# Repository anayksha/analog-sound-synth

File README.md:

# Analog sound synth

I think its analog idk

TODO: write readme

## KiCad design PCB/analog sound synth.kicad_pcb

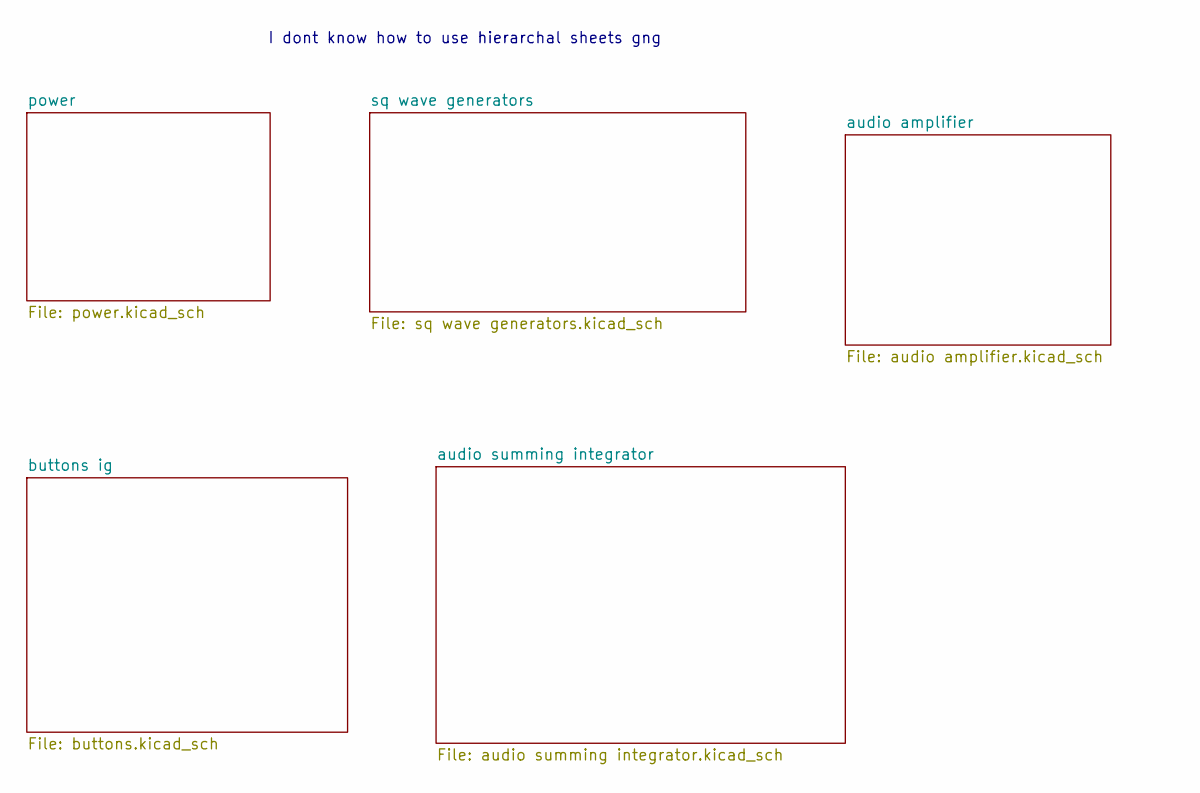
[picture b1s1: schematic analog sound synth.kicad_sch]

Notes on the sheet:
I dont know how to use hierarchal sheets gng

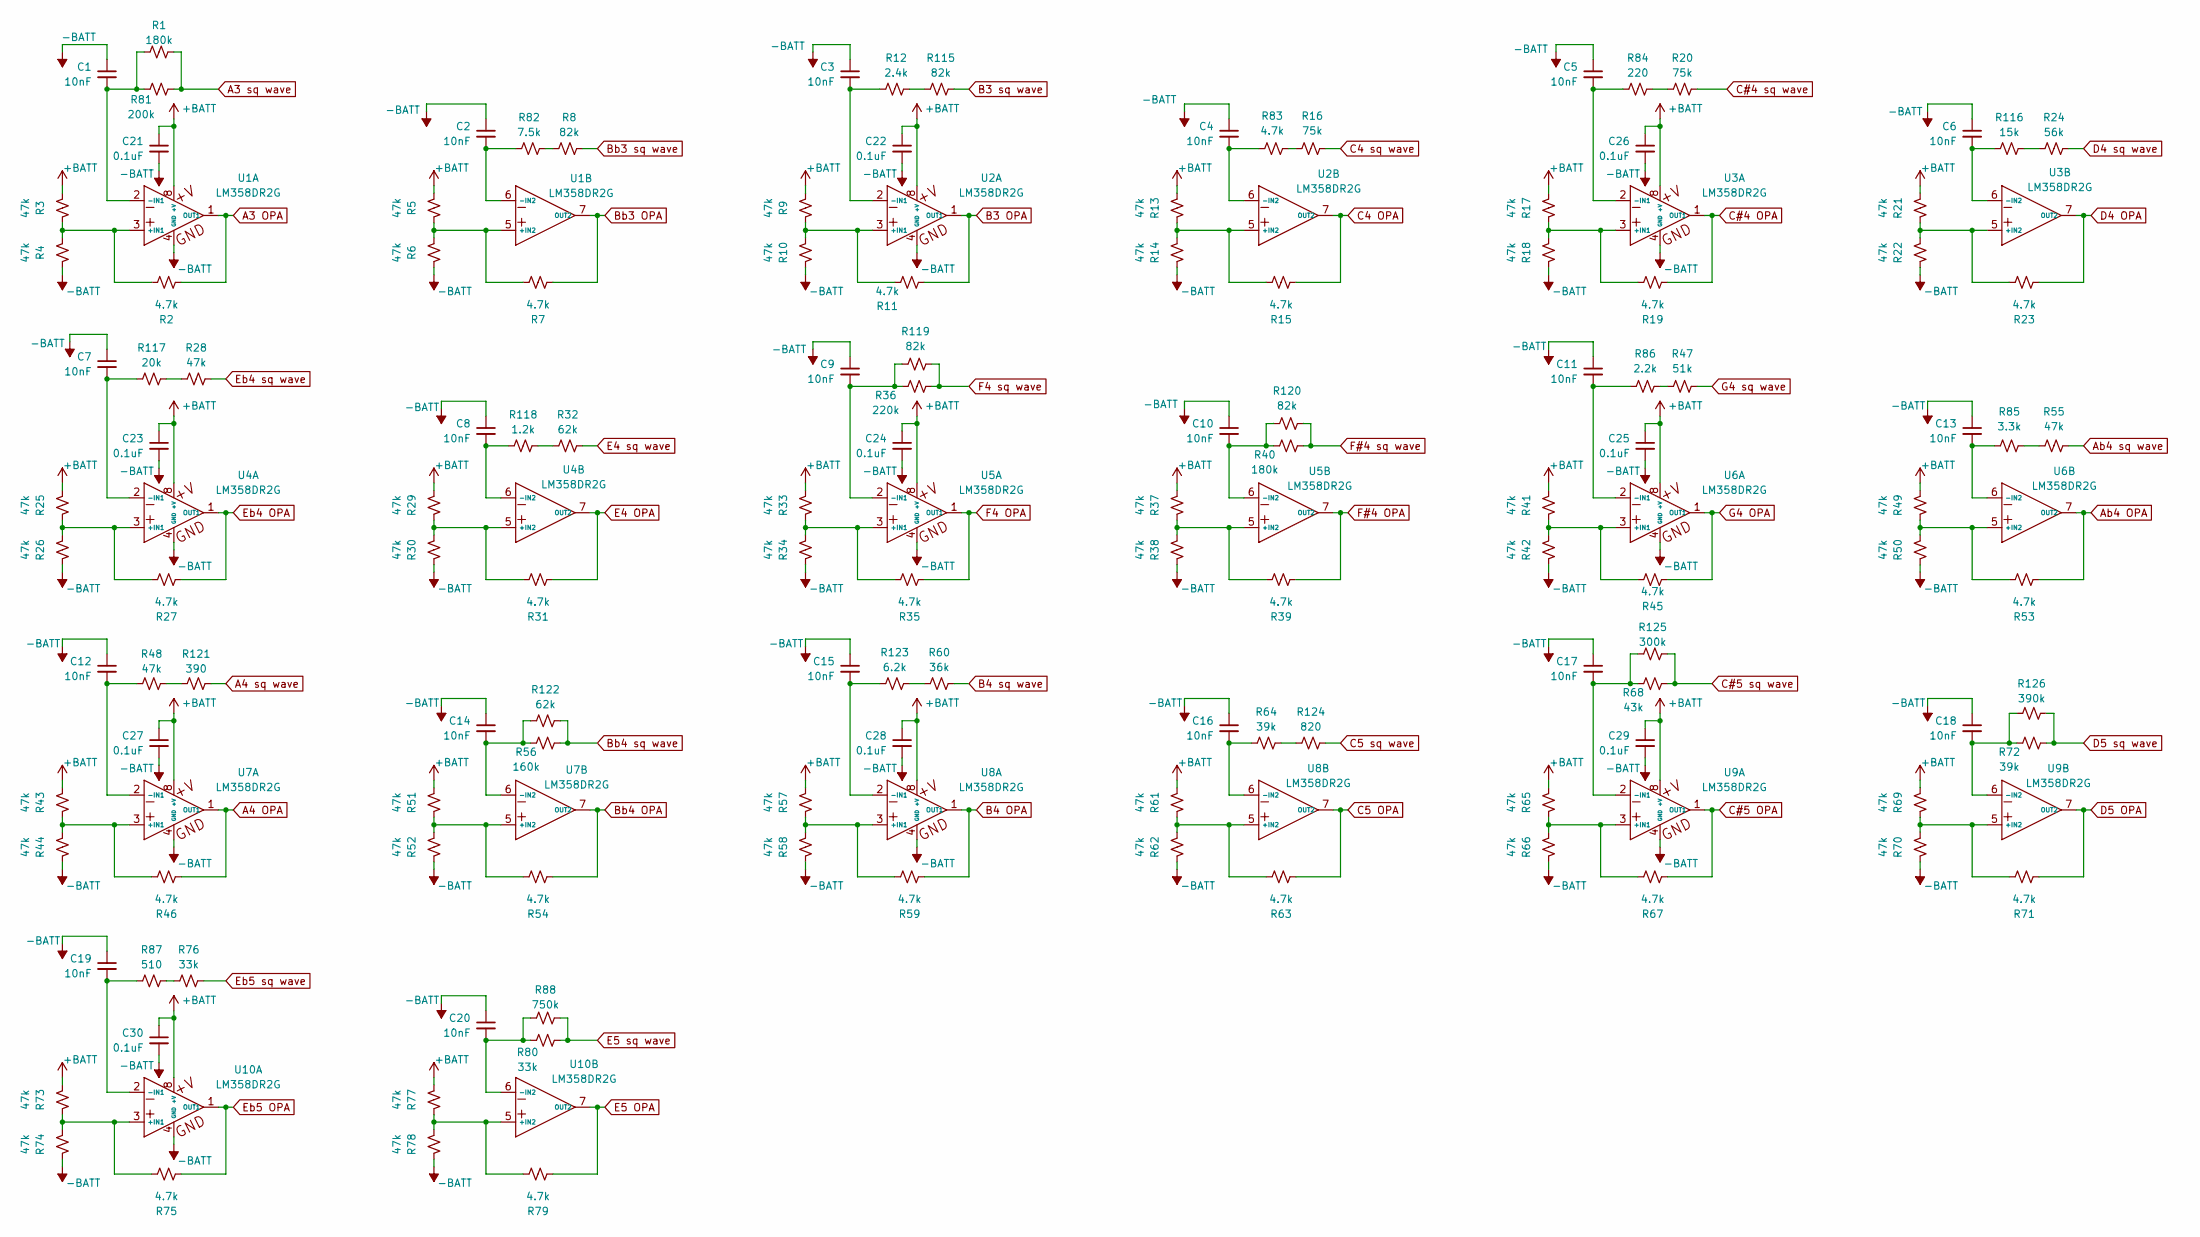
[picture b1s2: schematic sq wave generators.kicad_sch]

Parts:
C1, C2, C3, C4, C5, C6, C7, C8, C9, C10, C11, C12, C13, C14, C15, C16, C17, C18, C19, C20: 10nF; C_0603_1608Metric
C21, C22, C23, C24, C25, C26, C27, C28, C29, C30: 0.1uF; C_0402_1005Metric
R1, R40: 180k; R_0603_1608Metric
R2, R7, R11, R15, R19, R23, R27, R31, R35, R39, R45, R46, R53, R54, R59, R63, R67, R71, R75, R79, R83: 4.7k; R_0402_1005Metric
R3, R4, R5, R6, R9, R10, R13, R14, R17, R18, R21, R22, R25, R26, R28, R29, R30, R33, R34, R37, R38, R41, R42, R43, R44, R48, R49, R50, R51, R52, R55, R57, R58, R61, R62, R65, R66, R69, R70, R73, R74, R77, R78: 47k; R_0402_1005Metric
R8, R115, R119, R120: 82k; R_0603_1608Metric
R12: 2.4k; R_0402_1005Metric
R16, R20: 75k; R_0402_1005Metric
R24: 56k; R_0402_1005Metric
R32, R122: 62k; R_0603_1608Metric
R36: 220k; R_0402_1005Metric
R47: 51k; R_0402_1005Metric
R56: 160k; R_0603_1608Metric
R60: 36k; R_0603_1608Metric
R64, R72: 39k; R_0402_1005Metric
R68: 43k; R_0603_1608Metric
R76, R80: 33k; R_0402_1005Metric
R81: 200k; R_0402_1005Metric
R82: 7.5k; R_0402_1005Metric
R84: 220; R_0402_1005Metric
R85: 3.3k; R_0402_1005Metric
R86: 2.2k; R_0402_1005Metric
R87: 510; R_0402_1005Metric
R88: 750k; R_0603_1608Metric
R116: 15k; R_0402_1005Metric
R117: 20k; R_0402_1005Metric
R118: 1.2k; R_0402_1005Metric
R121: 390; R_0603_1608Metric
R123: 6.2k; R_0603_1608Metric
R124: 820; R_0603_1608Metric
R125: 300k; R_0402_1005Metric
R126: 390k; R_0603_1608Metric
U1, U2, U3, U4, U5, U6, U7, U8, U9, U10: LM358DR2G; SOIC-8_L5.0-W4.0-P1.27-LS6.0-BL; MPN LM358DR2G; LCSC Part C7950

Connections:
+BATT: C21.1, C22.1, C23.1, C24.1, C25.1, C26.1, C27.1, C28.1, C29.1, C30.1, R3.2, R5.2, R9.2, R13.2, R17.2, R21.2, R25.2, R29.2, R33.2, R37.2, R41.2, R43.2, R49.2, R51.2, R57.2, R61.2, R65.2, R69.2, R73.2, R77.2, U1.8 (+V), U2.8 (+V), U3.8 (+V), U4.8 (+V), U5.8 (+V), U6.8 (+V), U7.8 (+V), U8.8 (+V), U9.8 (+V), U10.8 (+V); also elsewhere on the board
-BATT: C1.1, C2.1, C3.1, C4.1, C5.1, C6.1, C7.1, C8.1, C9.1, C10.1, C11.1, C12.1, C13.1, C14.1, C15.1, C16.1, C17.1, C18.1, C19.1, C20.1, C21.2, C22.2, C23.2, C24.2, C25.2, C26.2, C27.2, C28.2, C29.2, C30.2, R4.1, R6.1, R10.1, R14.1, R18.1, R22.1, R26.1, R30.1, R34.1, R38.1, R42.1, R44.1, R50.1, R52.1, R58.1, R62.1, R66.1, R70.1, R74.1, R78.1, U1.4 (GND), U2.4 (GND), U3.4 (GND), U4.4 (GND), U5.4 (GND), U6.4 (GND), U7.4 (GND), U8.4 (GND), U9.4 (GND), U10.4 (GND); also elsewhere on the board
A3 OPA: R2.2, U1.1 (OUT1); also elsewhere on the board
A3 sq wave: R1.2, R81.2; also elsewhere on the board
A4 OPA: R46.2, U7.1 (OUT1); also elsewhere on the board
A4 sq wave: R121.2; also elsewhere on the board
Ab4 OPA: R53.2, U6.7 (OUT2); also elsewhere on the board
Ab4 sq wave: R55.2; also elsewhere on the board
B3 OPA: R11.2, U2.1 (OUT1); also elsewhere on the board
B3 sq wave: R115.2; also elsewhere on the board
B4 OPA: R59.2, U8.1 (OUT1); also elsewhere on the board
B4 sq wave: R60.2; also elsewhere on the board
Bb3 OPA: R7.2, U1.7 (OUT2); also elsewhere on the board
Bb3 sq wave: R8.2; also elsewhere on the board
Bb4 OPA: R54.2, U7.7 (OUT2); also elsewhere on the board
Bb4 sq wave: R56.2, R122.2; also elsewhere on the board
C4 OPA: R15.2, U2.7 (OUT2); also elsewhere on the board
C4 sq wave: R16.2; also elsewhere on the board
C5 OPA: R63.2, U8.7 (OUT2); also elsewhere on the board
C5 sq wave: R124.2; also elsewhere on the board
C#4 OPA: R19.2, U3.1 (OUT1); also elsewhere on the board
C#4 sq wave: R20.2; also elsewhere on the board
C#5 OPA: R67.2, U9.1 (OUT1); also elsewhere on the board
C#5 sq wave: R68.2, R125.2; also elsewhere on the board
D4 OPA: R23.2, U3.7 (OUT2); also elsewhere on the board
D4 sq wave: R24.2; also elsewhere on the board
D5 OPA: R71.2, U9.7 (OUT2); also elsewhere on the board
D5 sq wave: R72.2, R126.2; also elsewhere on the board
E4 OPA: R31.2, U4.7 (OUT2); also elsewhere on the board
E4 sq wave: R32.2; also elsewhere on the board
E5 OPA: R79.2, U10.7 (OUT2); also elsewhere on the board
E5 sq wave: R80.2, R88.2; also elsewhere on the board
Eb4 OPA: R27.2, U4.1 (OUT1); also elsewhere on the board
Eb4 sq wave: R28.2; also elsewhere on the board
Eb5 OPA: R75.2, U10.1 (OUT1); also elsewhere on the board
Eb5 sq wave: R76.2; also elsewhere on the board
F4 OPA: R35.2, U5.1 (OUT1); also elsewhere on the board
F4 sq wave: R36.2, R119.2; also elsewhere on the board
F#4 OPA: R39.2, U5.7 (OUT2); also elsewhere on the board
F#4 sq wave: R40.2, R120.2; also elsewhere on the board
G4 OPA: R45.2, U6.1 (OUT1); also elsewhere on the board
G4 sq wave: R47.2; also elsewhere on the board
unnamed: R8.1, R82.2
unnamed: R16.1, R83.2
unnamed: R20.1, R84.2
unnamed: R47.1, R86.2
unnamed: R55.1, R85.2
unnamed: R76.1, R87.2
unnamed: R12.2, R115.1
unnamed: R24.1, R116.2
unnamed: R28.1, R117.2
unnamed: R32.1, R118.2
unnamed: R48.2, R121.1
unnamed: R60.1, R123.2
unnamed: R64.2, R124.1
unnamed: R2.1, R3.1, R4.2, U1.3 (+IN1)
unnamed: C1.2, R1.1, R81.1, U1.2 (-IN1)
unnamed: R5.1, R6.2, R7.1, U1.5 (+IN2)
unnamed: C2.2, R82.1, U1.6 (-IN2)
unnamed: R9.1, R10.2, R11.1, U2.3 (+IN1)
unnamed: C3.2, R12.1, U2.2 (-IN1)
unnamed: R13.1, R14.2, R15.1, U2.5 (+IN2)
unnamed: C4.2, R83.1, U2.6 (-IN2)
unnamed: R17.1, R18.2, R19.1, U3.3 (+IN1)
unnamed: C5.2, R84.1, U3.2 (-IN1)
unnamed: R21.1, R22.2, R23.1, U3.5 (+IN2)
unnamed: C6.2, R116.1, U3.6 (-IN2)
unnamed: R25.1, R26.2, R27.1, U4.3 (+IN1)
unnamed: C7.2, R117.1, U4.2 (-IN1)
unnamed: R29.1, R30.2, R31.1, U4.5 (+IN2)
unnamed: C8.2, R118.1, U4.6 (-IN2)
unnamed: R33.1, R34.2, R35.1, U5.3 (+IN1)
unnamed: C9.2, R36.1, R119.1, U5.2 (-IN1)
unnamed: R37.1, R38.2, R39.1, U5.5 (+IN2)
unnamed: C10.2, R40.1, R120.1, U5.6 (-IN2)
unnamed: R41.1, R42.2, R45.1, U6.3 (+IN1)
unnamed: C11.2, R86.1, U6.2 (-IN1)
unnamed: R49.1, R50.2, R53.1, U6.5 (+IN2)
unnamed: C13.2, R85.1, U6.6 (-IN2)
unnamed: R43.1, R44.2, R46.1, U7.3 (+IN1)
unnamed: C12.2, R48.1, U7.2 (-IN1)
unnamed: R51.1, R52.2, R54.1, U7.5 (+IN2)
unnamed: C14.2, R56.1, R122.1, U7.6 (-IN2)
unnamed: R57.1, R58.2, R59.1, U8.3 (+IN1)
unnamed: C15.2, R123.1, U8.2 (-IN1)
unnamed: R61.1, R62.2, R63.1, U8.5 (+IN2)
unnamed: C16.2, R64.1, U8.6 (-IN2)
unnamed: R65.1, R66.2, R67.1, U9.3 (+IN1)
unnamed: C17.2, R68.1, R125.1, U9.2 (-IN1)
unnamed: R69.1, R70.2, R71.1, U9.5 (+IN2)
unnamed: C18.2, R72.1, R126.1, U9.6 (-IN2)
unnamed: R73.1, R74.2, R75.1, U10.3 (+IN1)
unnamed: C19.2, R87.1, U10.2 (-IN1)
unnamed: R77.1, R78.2, R79.1, U10.5 (+IN2)
unnamed: C20.2, R80.1, R88.1, U10.6 (-IN2)

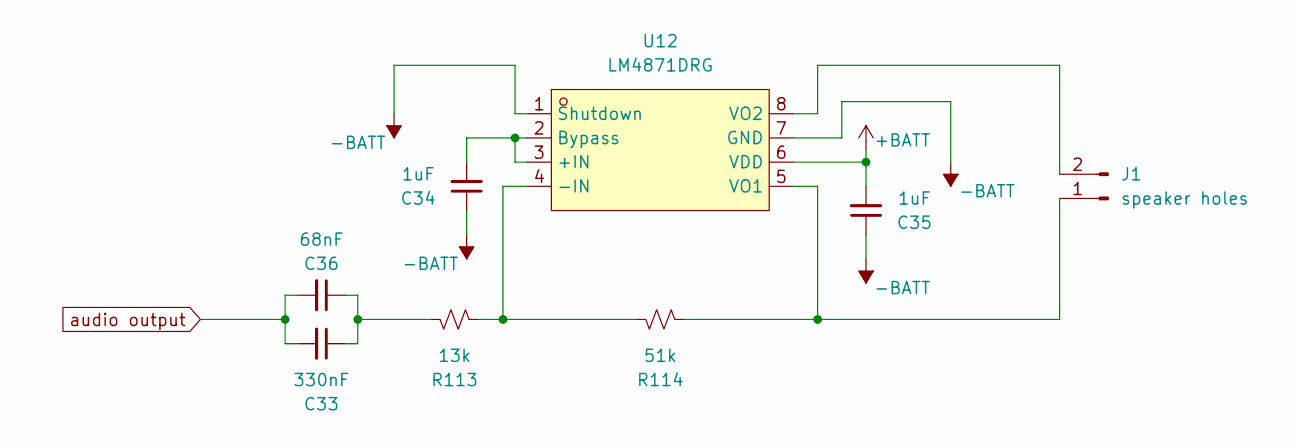
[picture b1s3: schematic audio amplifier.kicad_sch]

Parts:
C33: 330nF; C_0603_1608Metric
C34, C35: 1uF; C_0402_1005Metric
C36: 68nF; C_0603_1608Metric
J1: speaker holes; SolderWire-0.15sqmm_1x02_P4mm_D0.5mm_OD1.5mm_Relief
R113: 13k; R_0603_1608Metric
R114: 51k; R_0402_1005Metric
U12: LM4871DRG; SOP-8_L4.9-W3.9-P1.27-LS6.0-BL; MPN LM4871DRG; LCSC Part C2977084

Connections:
+BATT: C35.2, U12.6 (VDD); also elsewhere on the board
-BATT: C34.1, C35.1, U12.1 (Shutdown), U12.7 (GND); also elsewhere on the board
unnamed: C33.1, C36.1, R113.1
unnamed: J1.1, R114.2, U12.5 (VO1)
unnamed: J1.2, U12.8 (VO2)
unnamed: C34.2, U12.2 (Bypass), U12.3 (+IN)
unnamed: R113.2, R114.1, U12.4 (-IN)
audio output: C33.2, C36.2; also elsewhere on the board

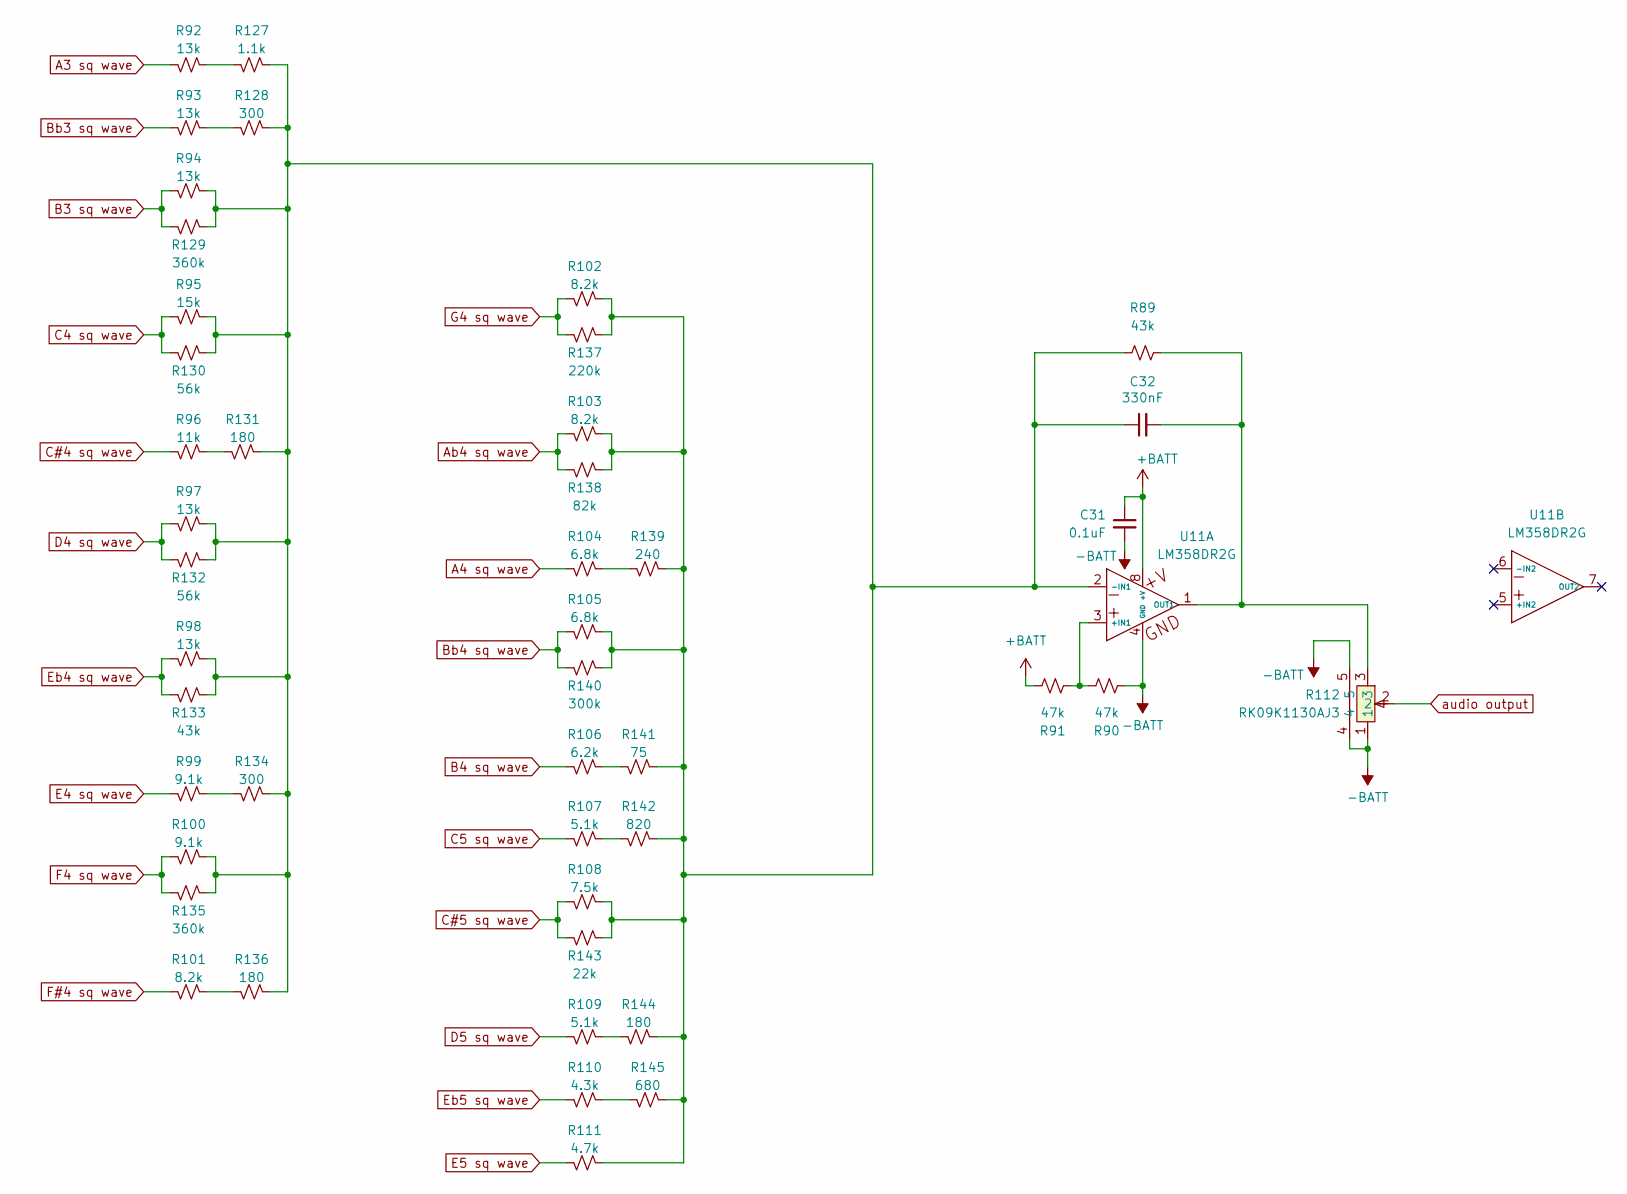
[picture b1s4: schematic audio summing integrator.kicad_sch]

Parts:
C31: 0.1uF; C_0402_1005Metric
C32: 330nF; C_0603_1608Metric
R89, R133: 43k; R_0603_1608Metric
R90, R91: 47k; R_0402_1005Metric
R92, R93, R94, R97, R98: 13k; R_0603_1608Metric
R95: 15k; R_0402_1005Metric
R96: 11k; R_0603_1608Metric
R99, R100: 9.1k; R_0603_1608Metric
R101, R102, R103: 8.2k; R_0402_1005Metric
R104, R105: 6.8k; R_0603_1608Metric
R106: 6.2k; R_0603_1608Metric
R107, R109: 5.1k; R_0402_1005Metric
R108: 7.5k; R_0402_1005Metric
R110: 4.3k; R_0603_1608Metric
R111: 4.7k; R_0402_1005Metric
R112: RK09K1130AJ3; RES-ADJ-TH_RK09K1130AJ3; MPN RK09K1130AJ3; LCSC Part C388854
R127: 1.1k; R_0603_1608Metric
R128, R134: 300; R_0402_1005Metric
R129, R135: 360k; R_0603_1608Metric
R130, R132: 56k; R_0402_1005Metric
R131, R136, R144: 180; R_0603_1608Metric
R137: 220k; R_0402_1005Metric
R138: 82k; R_0603_1608Metric
R139: 240; R_0603_1608Metric
R140: 300k; R_0402_1005Metric
R141: 75; R_0402_1005Metric
R142: 820; R_0603_1608Metric
R143: 22k; R_0402_1005Metric
R145: 680; R_0402_1005Metric
U11: LM358DR2G; SOIC-8_L5.0-W4.0-P1.27-LS6.0-BL; MPN LM358DR2G; LCSC Part C7950

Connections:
+BATT: C31.1, R91.2, U11.8 (+V); also elsewhere on the board
-BATT: C31.2, R90.1, R112.1, R112.4, R112.5, U11.4 (GND); also elsewhere on the board
A3 sq wave: R92.2; also elsewhere on the board
A4 sq wave: R104.2; also elsewhere on the board
Ab4 sq wave: R103.2, R138.2; also elsewhere on the board
B3 sq wave: R94.2, R129.2; also elsewhere on the board
B4 sq wave: R106.2; also elsewhere on the board
Bb3 sq wave: R93.2; also elsewhere on the board
Bb4 sq wave: R105.2, R140.2; also elsewhere on the board
C4 sq wave: R95.2, R130.2; also elsewhere on the board
C5 sq wave: R107.2; also elsewhere on the board
C#4 sq wave: R96.2; also elsewhere on the board
C#5 sq wave: R108.2, R143.2; also elsewhere on the board
D4 sq wave: R97.2, R132.2; also elsewhere on the board
D5 sq wave: R109.2; also elsewhere on the board
E4 sq wave: R99.2; also elsewhere on the board
E5 sq wave: R111.2; also elsewhere on the board
Eb4 sq wave: R98.2, R133.2; also elsewhere on the board
Eb5 sq wave: R110.2; also elsewhere on the board
F4 sq wave: R100.2, R135.2; also elsewhere on the board
F#4 sq wave: R101.2; also elsewhere on the board
G4 sq wave: R102.2, R137.2; also elsewhere on the board
unnamed: R101.1, R136.2
unnamed: R104.1, R139.2
unnamed: R106.1, R141.2
unnamed: R107.1, R142.2
unnamed: R109.1, R144.2
unnamed: R110.1, R145.2
unnamed: R92.1, R127.2
unnamed: R93.1, R128.2
unnamed: R96.1, R131.2
unnamed: R99.1, R134.2
unnamed: R90.2, R91.1, U11.3 (+IN1)
unnamed: C32.1, R89.1, R94.1, R95.1, R97.1, R98.1, R100.1, R102.1, R103.1, R105.1, R108.1, R111.1, R127.1, R128.1, R129.1, R130.1, R131.1, R132.1, R133.1, R134.1, R135.1, R136.1, R137.1, R138.1, R139.1, R140.1, R141.1, R142.1, R143.1, R144.1, R145.1, U11.2 (-IN1)
unnamed: C32.2, R89.2, R112.3, U11.1 (OUT1)
audio output: R112.2; also elsewhere on the board

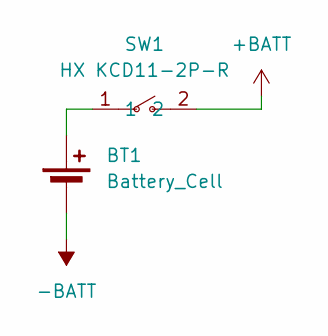
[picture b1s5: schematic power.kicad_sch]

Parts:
BT1: Battery_Cell; SolderWire-0.15sqmm_1x02_P4mm_D0.5mm_OD1.5mm_Relief
SW1: HX KCD11-2P-R; SW-TH_2P-L15.0-W10.5-P5.00_KCD11-2P-R; MPN HX KCD11-2P-R; LCSC Part C6917318

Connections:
+BATT: SW1.2; also elsewhere on the board
-BATT: BT1.2 (-); also elsewhere on the board
unnamed: BT1.1 (+), SW1.1

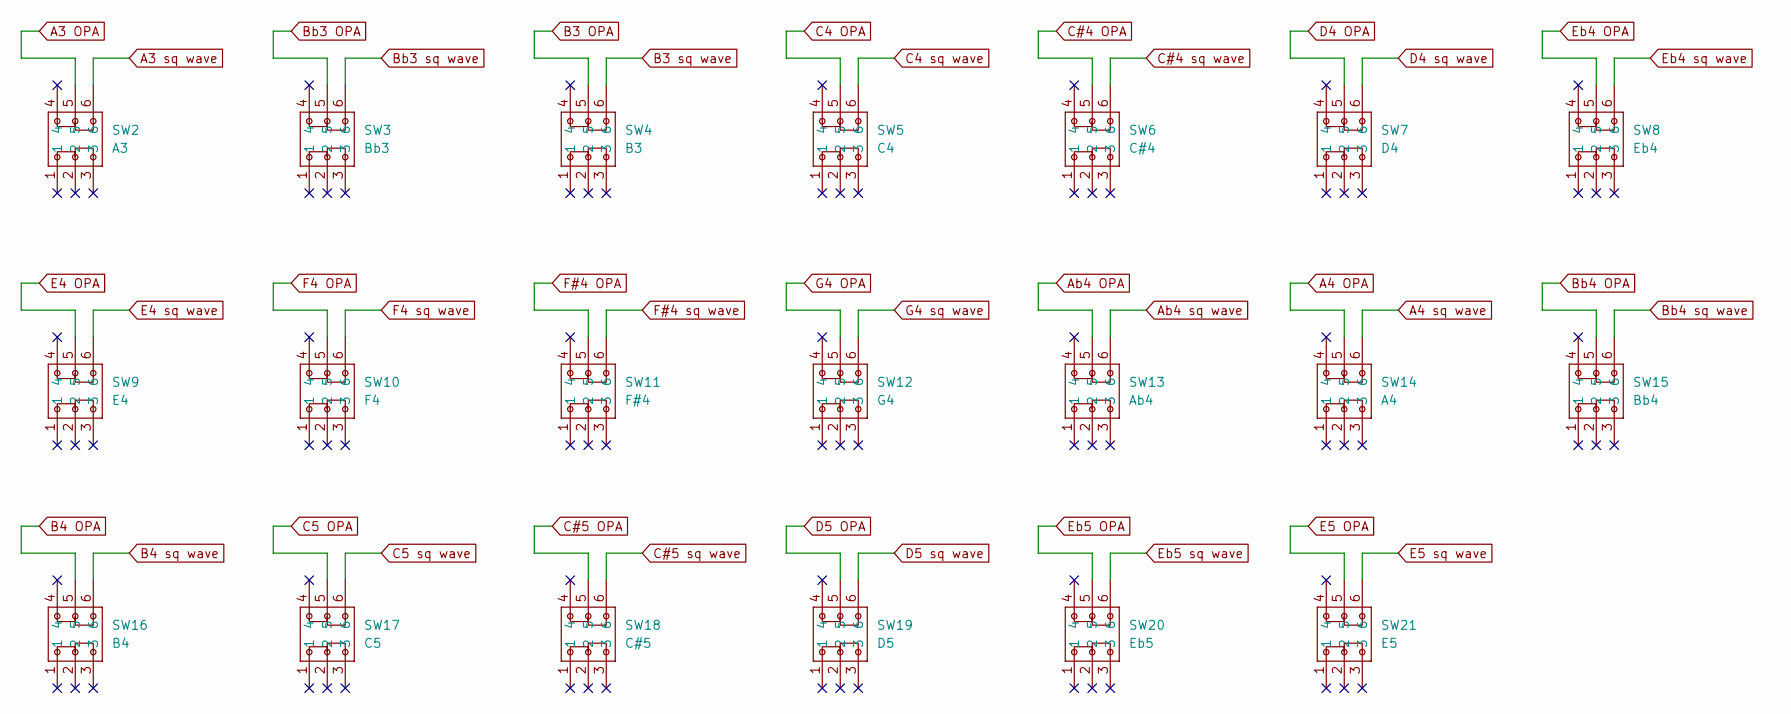
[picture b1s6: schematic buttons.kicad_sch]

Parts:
SW2: A3; SW-TH_6P-L7.0-W7.0-P2.00; MPN PS-7054DVB-6PN; LCSC Part C22363820
SW3: Bb3; SW-TH_6P-L7.0-W7.0-P2.00; MPN PS-7054DVB-6PN; LCSC Part C22363820
SW4: B3; SW-TH_6P-L7.0-W7.0-P2.00; MPN PS-7054DVB-6PN; LCSC Part C22363820
SW5: C4; SW-TH_6P-L7.0-W7.0-P2.00; MPN PS-7054DVB-6PN; LCSC Part C22363820
SW6: C#4; SW-TH_6P-L7.0-W7.0-P2.00; MPN PS-7054DVB-6PN; LCSC Part C22363820
SW7: D4; SW-TH_6P-L7.0-W7.0-P2.00; MPN PS-7054DVB-6PN; LCSC Part C22363820
SW8: Eb4; SW-TH_6P-L7.0-W7.0-P2.00; MPN PS-7054DVB-6PN; LCSC Part C22363820
SW9: E4; SW-TH_6P-L7.0-W7.0-P2.00; MPN PS-7054DVB-6PN; LCSC Part C22363820
SW10: F4; SW-TH_6P-L7.0-W7.0-P2.00; MPN PS-7054DVB-6PN; LCSC Part C22363820
SW11: F#4; SW-TH_6P-L7.0-W7.0-P2.00; MPN PS-7054DVB-6PN; LCSC Part C22363820
SW12: G4; SW-TH_6P-L7.0-W7.0-P2.00; MPN PS-7054DVB-6PN; LCSC Part C22363820
SW13: Ab4; SW-TH_6P-L7.0-W7.0-P2.00; MPN PS-7054DVB-6PN; LCSC Part C22363820
SW14: A4; SW-TH_6P-L7.0-W7.0-P2.00; MPN PS-7054DVB-6PN; LCSC Part C22363820
SW15: Bb4; SW-TH_6P-L7.0-W7.0-P2.00; MPN PS-7054DVB-6PN; LCSC Part C22363820
SW16: B4; SW-TH_6P-L7.0-W7.0-P2.00; MPN PS-7054DVB-6PN; LCSC Part C22363820
SW17: C5; SW-TH_6P-L7.0-W7.0-P2.00; MPN PS-7054DVB-6PN; LCSC Part C22363820
SW18: C#5; SW-TH_6P-L7.0-W7.0-P2.00; MPN PS-7054DVB-6PN; LCSC Part C22363820
SW19: D5; SW-TH_6P-L7.0-W7.0-P2.00; MPN PS-7054DVB-6PN; LCSC Part C22363820
SW20: Eb5; SW-TH_6P-L7.0-W7.0-P2.00; MPN PS-7054DVB-6PN; LCSC Part C22363820
SW21: E5; SW-TH_6P-L7.0-W7.0-P2.00; MPN PS-7054DVB-6PN; LCSC Part C22363820

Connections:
A3 OPA: SW2.5; also elsewhere on the board
A3 sq wave: SW2.6; also elsewhere on the board
A4 OPA: SW14.5; also elsewhere on the board
A4 sq wave: SW14.6; also elsewhere on the board
Ab4 OPA: SW13.5; also elsewhere on the board
Ab4 sq wave: SW13.6; also elsewhere on the board
B3 OPA: SW4.5; also elsewhere on the board
B3 sq wave: SW4.6; also elsewhere on the board
B4 OPA: SW16.5; also elsewhere on the board
B4 sq wave: SW16.6; also elsewhere on the board
Bb3 OPA: SW3.5; also elsewhere on the board
Bb3 sq wave: SW3.6; also elsewhere on the board
Bb4 OPA: SW15.5; also elsewhere on the board
Bb4 sq wave: SW15.6; also elsewhere on the board
C4 OPA: SW5.5; also elsewhere on the board
C4 sq wave: SW5.6; also elsewhere on the board
C5 OPA: SW17.5; also elsewhere on the board
C5 sq wave: SW17.6; also elsewhere on the board
C#4 OPA: SW6.5; also elsewhere on the board
C#4 sq wave: SW6.6; also elsewhere on the board
C#5 OPA: SW18.5; also elsewhere on the board
C#5 sq wave: SW18.6; also elsewhere on the board
D4 OPA: SW7.5; also elsewhere on the board
D4 sq wave: SW7.6; also elsewhere on the board
D5 OPA: SW19.5; also elsewhere on the board
D5 sq wave: SW19.6; also elsewhere on the board
E4 OPA: SW9.5; also elsewhere on the board
E4 sq wave: SW9.6; also elsewhere on the board
E5 OPA: SW21.5; also elsewhere on the board
E5 sq wave: SW21.6; also elsewhere on the board
Eb4 OPA: SW8.5; also elsewhere on the board
Eb4 sq wave: SW8.6; also elsewhere on the board
Eb5 OPA: SW20.5; also elsewhere on the board
Eb5 sq wave: SW20.6; also elsewhere on the board
F4 OPA: SW10.5; also elsewhere on the board
F4 sq wave: SW10.6; also elsewhere on the board
F#4 OPA: SW11.5; also elsewhere on the board
F#4 sq wave: SW11.6; also elsewhere on the board
G4 OPA: SW12.5; also elsewhere on the board
G4 sq wave: SW12.6; also elsewhere on the board

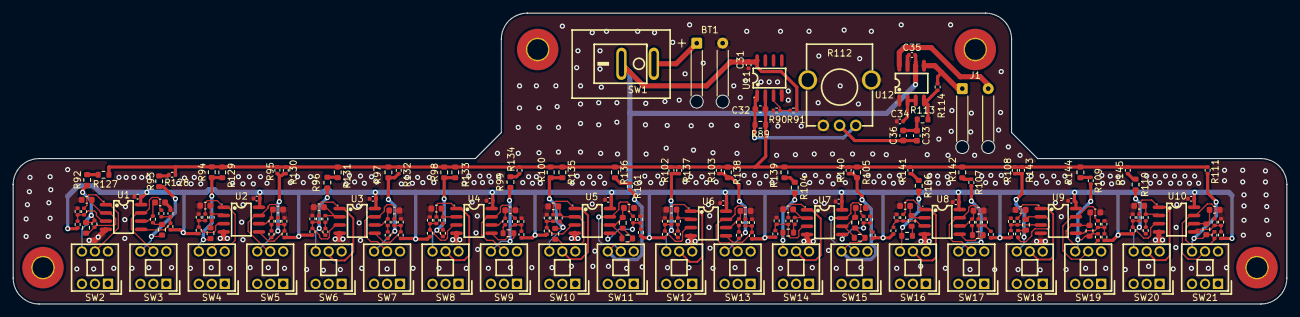
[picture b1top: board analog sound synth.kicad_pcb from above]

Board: 2 copper layers, 196.2 x 44.8 mm, 216 parts (0 on the bottom side), 115 nets.

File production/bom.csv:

Designator,Footprint,Quantity,Value,LCSC Part #
BT1,SolderWire-0.15sqmm_1x02_P4mm_D0.5mm_OD1.5mm_Relief,1,Battery_Cell,
"C1, C10, C11, C12, C13, C14, C15, C16, C17, C18, C19, C2, C20, C3, C4, C5, C6, C7, C8, C9",0603,20,10nF,
"C21, C22, C23, C24, C25, C26, C27, C28, C29, C30, C31",0402,11,0.1uF,
"C32, C33",0603,2,330nF,
"C34, C35",0402,2,1uF,
C36,0603,1,68nF,
J1,SolderWire-0.15sqmm_1x02_P4mm_D0.5mm_OD1.5mm_Relief,1,speaker holes,
"R1, R40",0603,2,180k,
"R10, R13, R14, R17, R18, R21, R22, R25, R26, R28, R29, R3, R30, R33, R34, R37, R38, R4, R41, R42, R43, R44, R48, R49, R5, R50, R51, R52, R55, R57, R58, R6, R61, R62, R65, R66, R69, R70, R73, R74, R77, R78, R9, R90, R91",0402,45,47k,
"R100, R99",0603,2,9.1k,
"R101, R102, R103",0402,3,8.2k,
"R104, R105",0603,2,6.8k,
"R106, R123",0603,2,6.2k,
"R107, R109",0402,2,5.1k,
"R108, R82",0402,2,7.5k,
"R11, R111, R15, R19, R2, R23, R27, R31, R35, R39, R45, R46, R53, R54, R59, R63, R67, R7, R71, R75, R79, R83",0402,22,4.7k,
R110,0603,1,4.3k,
R112,RES-ADJ-TH_RK09K1130AJ3,1,RK09K1130AJ3,C388854
"R113, R92, R93, R94, R97, R98",0603,6,13k,
"R114, R47",0402,2,51k,
"R115, R119, R120, R138, R8",0603,5,82k,
"R116, R95",0402,2,15k,
R117,0402,1,20k,
R118,0402,1,1.2k,
R12,0402,1,2.4k,
R121,0603,1,390,
"R122, R32",0603,2,62k,
"R124, R142",0603,2,820,
"R125, R140",0402,2,300k,
R126,0603,1,390k,
R127,0603,1,1.1k,
"R128, R134",0402,2,300,
"R129, R135",0603,2,360k,
"R130, R132, R24",0402,3,56k,
"R131, R136, R144",0603,3,180,
"R133, R68, R89",0603,3,43k,
"R137, R36",0402,2,220k,
R139,0603,1,240,
R141,0402,1,75,
R143,0402,1,22k,
R145,0402,1,680,
"R16, R20",0402,2,75k,
R56,0603,1,160k,
R60,0603,1,36k,
"R64, R72",0402,2,39k,
"R76, R80",0402,2,33k,
R81,0402,1,200k,
R84,0402,1,220,
R85,0402,1,3.3k,
R86,0402,1,2.2k,
R87,0402,1,510,
R88,0603,1,750k,
R96,0603,1,11k,
SW1,SW-TH_2P-L15.0-W10.5-P5.00_KCD11-2P-R,1,HX KCD11-2P-R,C6917318
SW10,SW-TH_6P-L7.0-W7.0-P2.00,1,F4,C22363820
SW11,SW-TH_6P-L7.0-W7.0-P2.00,1,F#4,C22363820
SW12,SW-TH_6P-L7.0-W7.0-P2.00,1,G4,C22363820
SW13,SW-TH_6P-L7.0-W7.0-P2.00,1,Ab4,C22363820
SW14,SW-TH_6P-L7.0-W7.0-P2.00,1,A4,C22363820
SW15,SW-TH_6P-L7.0-W7.0-P2.00,1,Bb4,C22363820
SW16,SW-TH_6P-L7.0-W7.0-P2.00,1,B4,C22363820
SW17,SW-TH_6P-L7.0-W7.0-P2.00,1,C5,C22363820
SW18,SW-TH_6P-L7.0-W7.0-P2.00,1,C#5,C22363820
SW19,SW-TH_6P-L7.0-W7.0-P2.00,1,D5,C22363820
SW2,SW-TH_6P-L7.0-W7.0-P2.00,1,A3,C22363820
SW20,SW-TH_6P-L7.0-W7.0-P2.00,1,Eb5,C22363820
SW21,SW-TH_6P-L7.0-W7.0-P2.00,1,E5,C22363820
SW3,SW-TH_6P-L7.0-W7.0-P2.00,1,Bb3,C22363820
SW4,SW-TH_6P-L7.0-W7.0-P2.00,1,B3,C22363820
SW5,SW-TH_6P-L7.0-W7.0-P2.00,1,C4,C22363820
SW6,SW-TH_6P-L7.0-W7.0-P2.00,1,C#4,C22363820
SW7,SW-TH_6P-L7.0-W7.0-P2.00,1,D4,C22363820
SW8,SW-TH_6P-L7.0-W7.0-P2.00,1,Eb4,C22363820
SW9,SW-TH_6P-L7.0-W7.0-P2.00,1,E4,C22363820
"U1, U10, U11, U2, U3, U4, U5, U6, U7, U8, U9",SOIC-8_L5.0-W4.0-P1.27-LS6.0-BL,11,LM358DR2G,C7950
U12,SOP-8_L4.9-W3.9-P1.27-LS6.0-BL,1,LM4871DRG,C2977084

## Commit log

2026-04-25 created project
2026-04-26 work session 1
    worked on button sub schematic and created rough design for op amp
    square wave oscillators without precise values
2026-05-13 I hate this
    so much
2026-05-23 basically entire pcb
    mainly added images for journal logs
